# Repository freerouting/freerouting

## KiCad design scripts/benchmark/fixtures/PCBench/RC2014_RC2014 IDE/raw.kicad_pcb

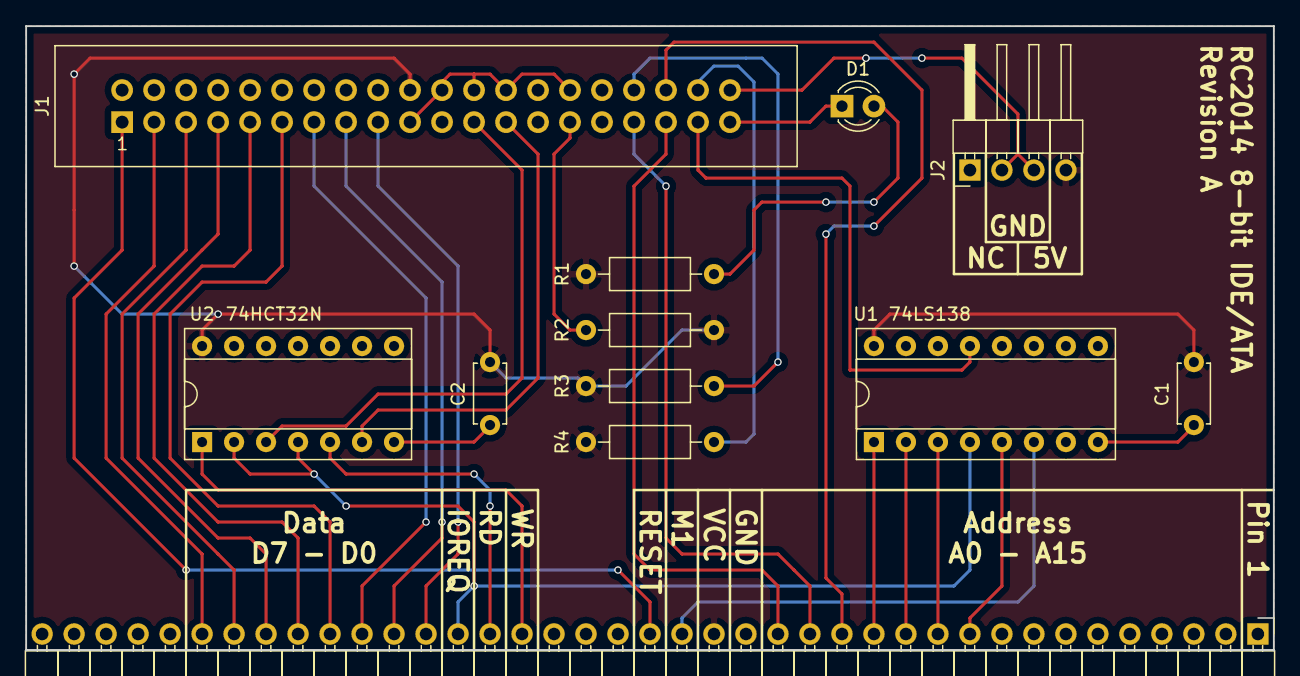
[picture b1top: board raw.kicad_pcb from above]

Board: 2 copper layers, 99.1 x 49.5 mm, 12 parts (0 on the bottom side), 30 nets.

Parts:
C1, C2: 100nF; C_Disc_D4.7mm_W2.5mm_P5.00mm
D1: LED; LED_D3.0mm
J1: CONN_02X20; IDC_Header_Straight_40pins
J2: Device power; Pin_Header_Angled_1x04_Pitch2.54mm
J4: CONN_01X39; Pin_Header_Angled_1x39_Pitch2.54mm
R1: 330; R_Axial_DIN0207_L6.3mm_D2.5mm_P10.16mm_Horizontal
R2, R3, R4: 1k; R_Axial_DIN0207_L6.3mm_D2.5mm_P10.16mm_Horizontal
U1: 74LS138; DIP-16_W7.62mm_Socket
U2: 74HCT32N; DIP-14_W7.62mm_Socket

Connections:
/IORD: J1.25, U2.6
/IOWR: J1.23, U2.3
A0: J1.35, J4.16
A1: J1.33, J4.15
A2: J1.36, J4.14
A3: J4.13, U1.1
A4: J4.12, U1.2
A5: J4.11, U1.3
A6: J4.10, U1.5
BUSY: D1.1, J1.39
D0: J1.17, J4.27
D1: J1.15, J4.28
D2: J1.13, J4.29
D3: J1.11, J4.30
D4: J1.9, J4.31
D5: J1.7, J4.32
D6: J1.5, J4.33
D7: J1.3, J4.34
GND: C1.2, C2.2, J1.2, J1.19, J1.22, J1.24, J1.26, J1.30, J1.40, J2.2, J2.3, J4.17, U1.8, U2.7, U2.9, U2.10, U2.12, U2.13
IOREQ: J4.26, U1.4, U2.2, U2.4
M1: J4.19, U1.6
unnamed: D1.2, R1.1
unnamed: J1.29, R2.1
unnamed: J1.34, R3.2
unnamed: J1.38, R4.2
PORT16: J1.37, U1.13
RD: J4.25, U2.5
RESET: J1.1, J4.20
VCC: C1.1, C2.1, J1.20, J2.4, J4.18, R1.2, R2.2, R3.1, R4.1, U1.16, U2.14
WR: J4.24, U2.1

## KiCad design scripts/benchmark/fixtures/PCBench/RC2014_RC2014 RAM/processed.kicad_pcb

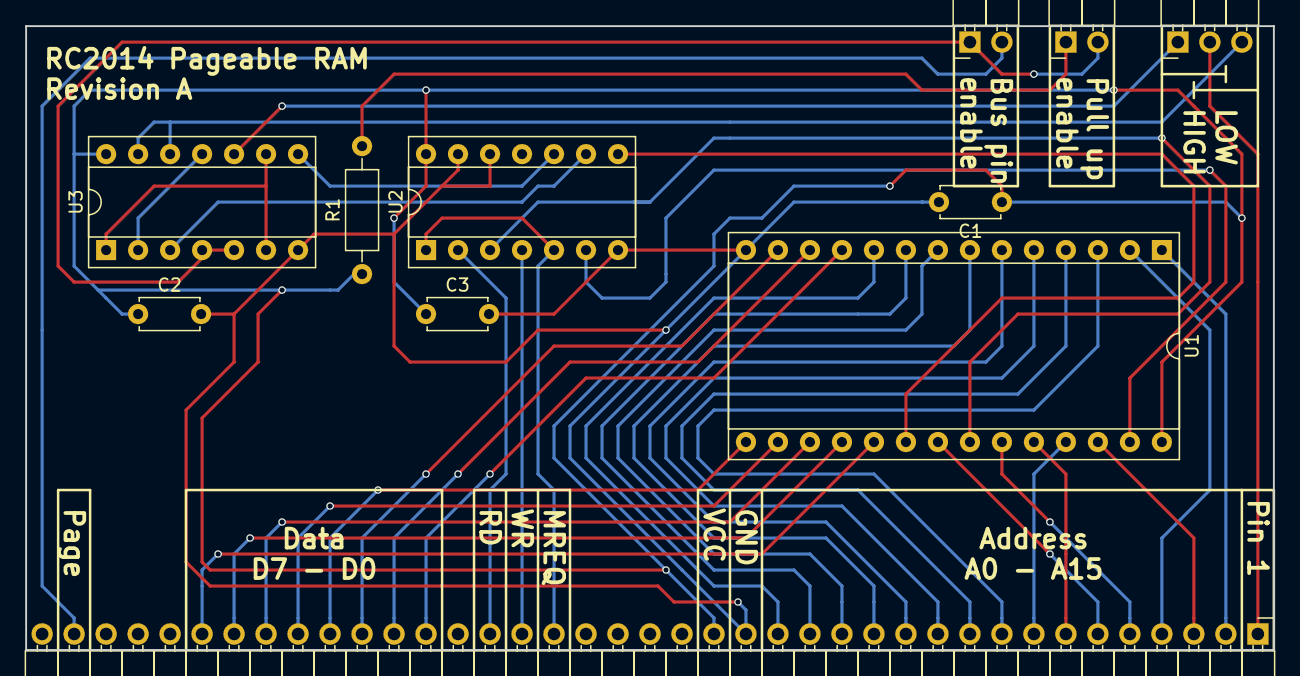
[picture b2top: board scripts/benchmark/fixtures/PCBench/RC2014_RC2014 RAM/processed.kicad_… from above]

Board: 2 copper layers, 99.1 x 49.5 mm, 11 parts (0 on the bottom side), 41 nets.

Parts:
C1, C2, C3: 100nF; C_Disc_D4.7mm_W2.5mm_P5.00mm
J1: Page PullUp; Pin_Header_Angled_1x02_Pitch2.54mm
J2: HIGH | LOW; Pin_Header_Angled_1x03_Pitch2.54mm
J3: Bus enable; Pin_Header_Angled_1x02_Pitch2.54mm
J4: CONN_01X39; Pin_Header_Angled_1x39_Pitch2.54mm
R1: 10k; R_Axial_DIN0207_L6.3mm_D2.5mm_P10.16mm_Horizontal
U1: HM62256BLP-7; DIP-28_W15.24mm_Socket
U2: 74LS32; DIP-14_W7.62mm_Socket
U3: 74HCT00; DIP-14_W7.62mm_Socket

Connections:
A0: J4.16, U1.10
A1: J4.15, U1.9
A2: J4.14, U1.8
A3: J4.13, U1.7
A4: J4.12, U1.6
A5: J4.11, U1.5
A6: J4.10, U1.4
A7: J4.9, U1.3
A8: J4.8, U1.25
A9: J4.7, U1.24
A10: J4.6, U1.21
A11: J4.5, U1.23
A12: J4.4, U1.2
A13: J4.3, U1.26
A14: J4.2, U1.1
A15: J2.2, J4.1
CS: U1.20, U2.8
D0: J4.27, U1.11
D1: J4.28, U1.12
D2: J4.29, U1.13
D3: J4.30, U1.15
D4: J4.31, U1.16
D5: J4.32, U1.17
D6: J4.33, U1.18
D7: J4.34, U1.19
EN: U3.1, U3.6, U3.9
GND: C1.2, C2.2, C3.2, J4.17, U1.14, U2.7, U2.12, U2.13, U3.7
HIGH: J2.1, U3.10
LOW: J2.3, U3.12, U3.13
MREQ: J4.23, U2.1, U2.5
unnamed: J1.1, R1.2
unnamed: J3.2, J4.38
unnamed: U1.22, U2.3
unnamed: U1.27, U2.6
unnamed: U2.9, U3.3
unnamed: U2.10, U3.8
unnamed: U3.2, U3.11
PAGE: J1.2, J3.1, U3.4, U3.5
RD: J4.25, U2.2
VCC: C1.1, C2.1, C3.1, J4.18, R1.1, U1.28, U2.14, U3.14
WR: J4.24, U2.4

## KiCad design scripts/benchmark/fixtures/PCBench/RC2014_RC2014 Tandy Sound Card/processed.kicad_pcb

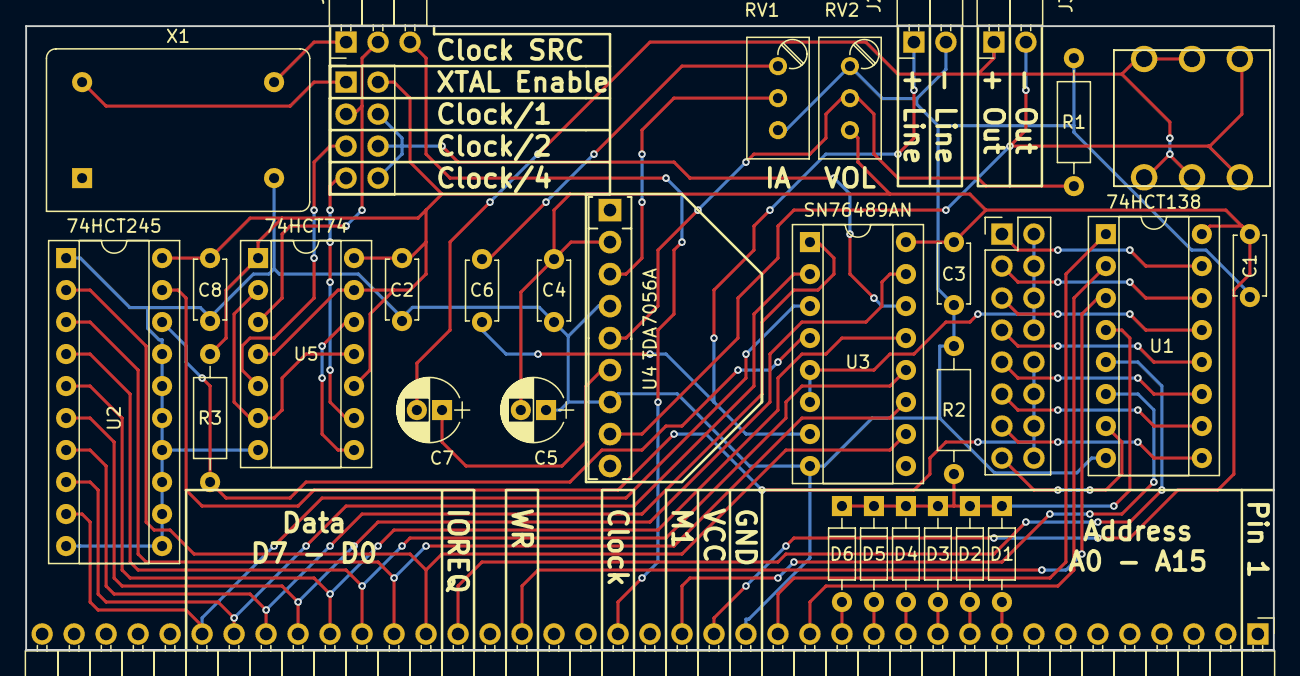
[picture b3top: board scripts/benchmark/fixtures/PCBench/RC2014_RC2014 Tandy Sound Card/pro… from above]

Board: 2 copper layers, 99.1 x 49.5 mm, 32 parts (0 on the bottom side), 49 nets.

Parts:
C1, C2, C3, C4, C8: 100nF; C_Disc_D4.7mm_W2.5mm_P5.00mm
C5: 220uF; CP_Radial_D5.0mm_P2.00mm
C6: 470nF; C_Disc_D4.7mm_W2.5mm_P5.00mm
C7: 470uF; CP_Radial_D5.0mm_P2.00mm
D1, D2, D3, D4, D5, D6: 1N4848; D_DO-35_SOD27_P7.62mm_Horizontal
J1: CONN_01X39; Pin_Header_Angled_1x39_Pitch2.54mm
J2: Line Out; Pin_Header_Angled_1x02_Pitch2.54mm
J3: Speaker Out; Pin_Header_Angled_1x02_Pitch2.54mm
J4: CONN_02X08; Pin_Header_Straight_2x08_Pitch2.54mm
J5: JACK_TRS_6PINS; cliff_fcr1295_socket
J6: CONN_02X04; Pin_Header_Straight_2x04_Pitch2.54mm
JP1: Clock source; Pin_Header_Angled_1x03_Pitch2.54mm
R1: 1k; R_Axial_DIN0207_L6.3mm_D2.5mm_P10.16mm_Horizontal
R2, R3: 10k; R_Axial_DIN0207_L6.3mm_D2.5mm_P10.16mm_Horizontal
RV1, RV2: 10k; Potentiometer_Trimmer_Bourns_3296W
U1: 74HCT138; DIP-16_W7.62mm_Socket
U2: 74HCT245; DIP-20_W7.62mm_Socket
U3: SN76489AN; DIP-16_W7.62mm_Socket
U4: TDA7056A; SIP9_Housing
U5: 74HCT74; DIP-14_W7.62mm_Socket
X1: 1MHz; Oscillator_DIP-14

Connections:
/RD_Port_0: J4.9, U1.11
/RD_Port_1: J4.11, U1.10
/RD_Port_2: J4.13, U1.9
/RD_Port_3: J4.15, U1.7
/WR_Port_0: J4.1, U1.15
/WR_Port_1: J4.3, U1.14
/WR_Port_2: J4.5, U1.13
/WR_Port_3: J4.7, U1.12
A0: J1.16, U1.1
A1: J1.15, U1.2
A2: D6.2, J1.14
A3: D5.2, J1.13
A4: D4.2, J1.12
A5: D3.2, J1.11
A6: D2.2, J1.10
A7: D1.2, J1.9
CLOCK: J1.21, JP1.3
CLOCK/1: J6.3, JP1.2, U5.3
CLOCK/2: J6.5, U5.5
CLOCK/4: J6.7, U5.9
D0: J1.27, U2.2, U3.10
D1: J1.28, U2.3, U3.11
D2: J1.29, U2.4, U3.12
D3: J1.30, U2.5, U3.13
D4: J1.31, U2.6, U3.15
D5: J1.32, U2.7, U3.1
D6: J1.33, U2.8, U3.2
D7: J1.34, U2.9, U3.3
GND: C1.2, C2.2, C3.2, C4.1, C5.1, C8.2, J1.17, J2.2, R1.2, R2.2, RV1.3, RV2.1, U1.8, U2.1, U2.10, U2.11, U2.12, U2.13, U2.14, U2.15, U2.16, U2.17, U3.8, U4.4, U4.7, U5.7, X1.7
IOREQ: J1.26, U1.5
IO_RD: J4.10, J4.12, J4.14, J4.16, U2.19
IO_WR: J4.2, J4.4, J4.6, J4.8, U3.5, U3.6
M1: J1.19, U1.6
unnamed: C6.2, RV1.1
unnamed: C7.2, J3.1, J5.2, J5.3, J5.5, J5.6
unnamed: D1.1, D2.1, D3.1, D4.1, D5.1, D6.1, R2.1, U1.4
unnamed: J6.1, X1.14
unnamed: JP1.1, X1.8
unnamed: R1.1, RV2.2, U4.5
unnamed: R3.2, U2.18, U3.4
unnamed: RV1.2, U4.3
unnamed: U5.2, U5.6, U5.11
unnamed: U5.8, U5.12
SND_CLOCK: J6.4, J6.6, J6.8, U3.14
SND_OUT: C6.1, J2.1, U3.7
SPKR_OUT+: C7.1, U4.6
SPKR_OUT-: J3.2, J5.1, J5.4, U4.8
VCC: C1.1, C2.1, C3.1, C4.2, C5.2, C8.1, J1.18, J6.2, R3.1, RV2.3, U1.16, U2.20, U3.16, U4.2, U5.1, U5.4, U5.10, U5.13, U5.14
WR: J1.24, U1.3
